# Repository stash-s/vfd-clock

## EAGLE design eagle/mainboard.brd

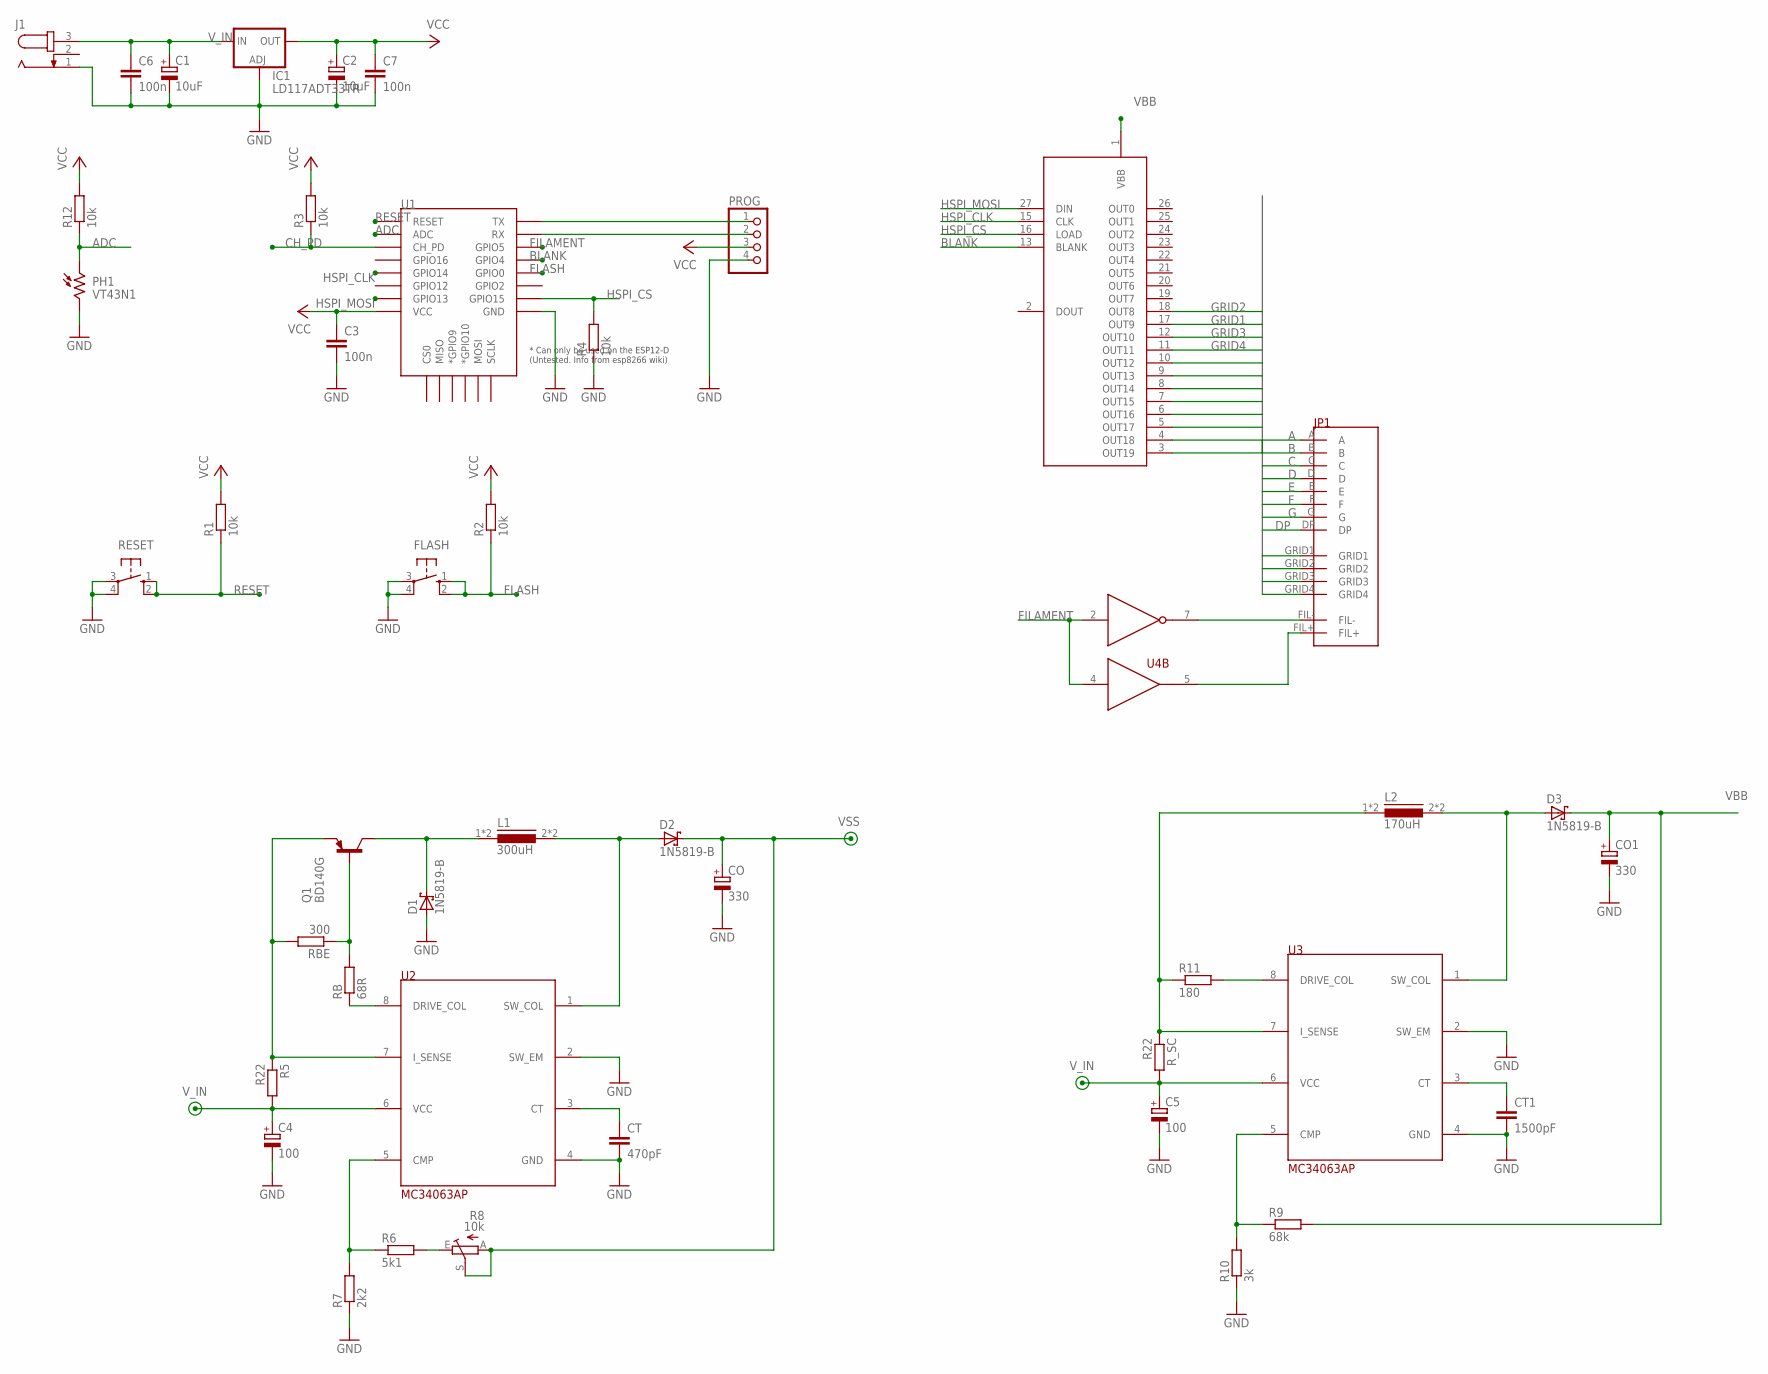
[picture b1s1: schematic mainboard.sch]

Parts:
C1, C2: 10uF; TT2D5L
C3, C6, C7: 100n; C050-024X044
C4, C5: 100; TT2D5L
CO: 330; TT5D11R
CO1: 330; TT5D11L
CT: 470pF; C025-025X050
CT1: 1500pF; C025-025X050
D1, D2, D3: 1N5819-B; DO41-7.6
FLASH: 10-XX; B3F-10XX
IC1: LD117ADT33TR; DPACK
J1: JACK-PLUG0; SPC4077
JP1: PINHD-2X102X10-MALE; 2X10
L1: 300uH; TOROID
L2: 170uH; TOROID
PH1: VT43N1; VT400
PROG: PINHD-1X4/90; 1X04/90
Q1: BD140G; TO225AA
R1, R12: 10k; 0207/15
R2, R4: 10k; 0204/7
R3: 10k; 0207/10
R5: R22; 0411/15
R6: 5k1; 0204/7
R7: 2k2; 0204/7
R8: 10k; S64W
R9: 68k; 0204/7
R10: 3k; 0204/7
R11: 180; 0204/7
RB: 68R; 0204/7
RBE: 300; 0204/7
RESET: 10-XX; B3F-10XX
R_SC: R22; 0411/15
U1: ESP12ESMD; ESP12E-SMD
U2, U3: MC34063AP; DIL8
U4: MAX628; DIL8
U$1: MAX6921AWI; SOP28X

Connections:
A: JP1.A, U$1.10 (OUT12)
ADC: PH1.1, R12.1, U1.ADC
B: JP1.B, U$1.9 (OUT13)
BLANK: U1.GPIO4, U$1.13 (BLANK)
C: JP1.C, U$1.8 (OUT14)
CH_PD: R3.1, U1.CH_PD
D: JP1.D, U$1.7 (OUT15)
DP: JP1.DP, U$1.3 (OUT19)
E: JP1.E, U$1.6 (OUT16)
F: JP1.F, U$1.5 (OUT17)
FIL+: JP1.FIL+, U4.5 (OUT)
FIL-: JP1.FIL-, U4.7 (OUT)
FILAMENT: U1.GPIO5, U4.2 (IN), U4.4 (IN)
FLASH: FLASH.1 (S), FLASH.2 (S1), R2.1, U1.GPIO0
G: JP1.G, U$1.4 (OUT18)
GND: C1.-, C2.-, C3.2, C4.-, C5.-, C6.2, C7.2, CO.-, CO1.-, CT.2, CT1.2, D1.A, FLASH.3, FLASH.4 (P1), IC1.1 (ADJ), J1.1, PH1.2, PROG.4, R4.1, R7.1, R10.1, RESET.3, RESET.4 (P1), U1.GND, U2.2 (SW_EM), U2.4 (GND), U3.2 (SW_EM), U3.4 (GND), U4.3 (GND), U$1.14 (GND)
GRID1: JP1.GRID1, U$1.17 (OUT9)
GRID2: JP1.GRID2, U$1.18 (OUT8)
GRID3: JP1.GRID3, U$1.12 (OUT10)
GRID4: JP1.GRID4, U$1.11 (OUT11)
HSPI_CLK: U1.GPIO14, U$1.15 (CLK)
HSPI_CS: R4.2, U1.GPIO15, U$1.16 (LOAD)
HSPI_MOSI: U1.GPIO13, U$1.27 (DIN)
unnamed: Q1.3 (B), RB.2, RBE.1
unnamed: RB.1, U2.8 (DRIVE_COL)
unnamed: Q1.1 (E), R5.1, RBE.2, U2.7 (I_SENSE)
unnamed: D2.A, L1.2, L1.2A (2), U2.1 (SW_COL)
unnamed: D1.C, L1.1, L1.1A (1), Q1.2 (C)
unnamed: CT.1, U2.3 (CT)
unnamed: R6.1, R7.2, U2.5 (CMP)
unnamed: R6.2, R8.E
unnamed: L2.1, L2.1A (1), R11.1, R_SC.1, U3.7 (I_SENSE)
unnamed: D3.A, L2.2, L2.2A (2), U3.1 (SW_COL)
unnamed: CT1.1, U3.3 (CT)
unnamed: R9.1, R10.2, U3.5 (CMP)
unnamed: R11.2, U3.8 (DRIVE_COL)
RESET: R1.1, RESET.1 (S), RESET.2 (S1), U1.RESET
RX: PROG.2, U1.RXD0 (RX)
TX: PROG.1, U1.TXD0 (TX)
VBB: CO1.+, D3.C, R9.2, U$1.1 (VBB)
VCC: C2.+, C3.1, C7.1, IC1.4 (OUT), PROG.3, R1.2, R2.2, R3.2, R12.2, U1.VCC, U$1.28 (VCC)
VSS: CO.+, D2.C, R8.A, R8.S, U4.6 (VSS)
V_IN: C1.+, C4.+, C5.+, C6.1, IC1.3 (IN), J1.3, R5.2, R_SC.2, U2.6 (VCC), U3.6 (VCC)

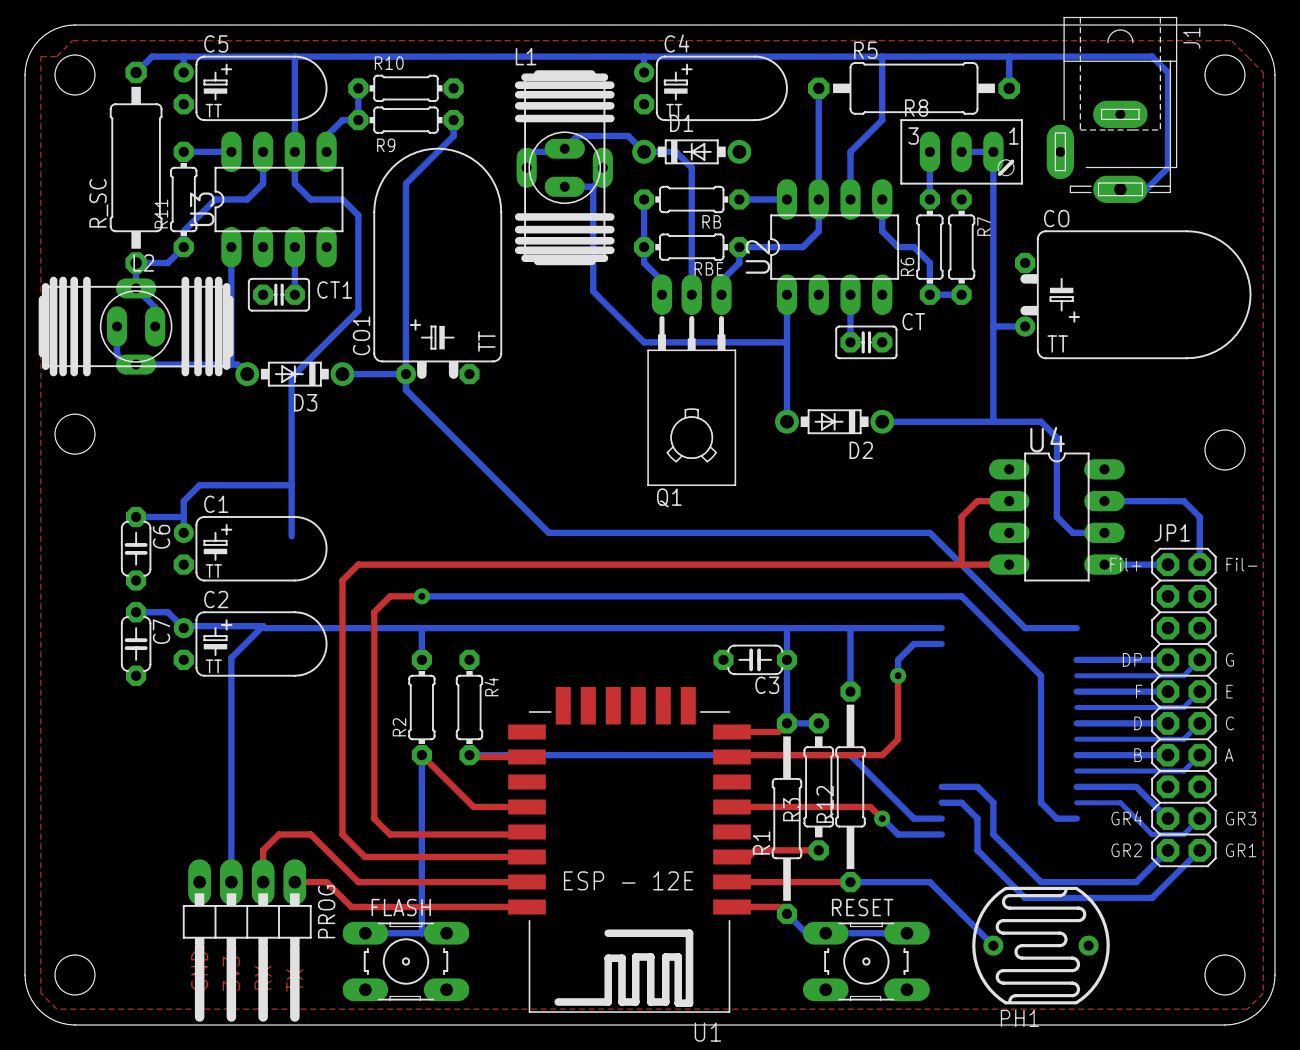
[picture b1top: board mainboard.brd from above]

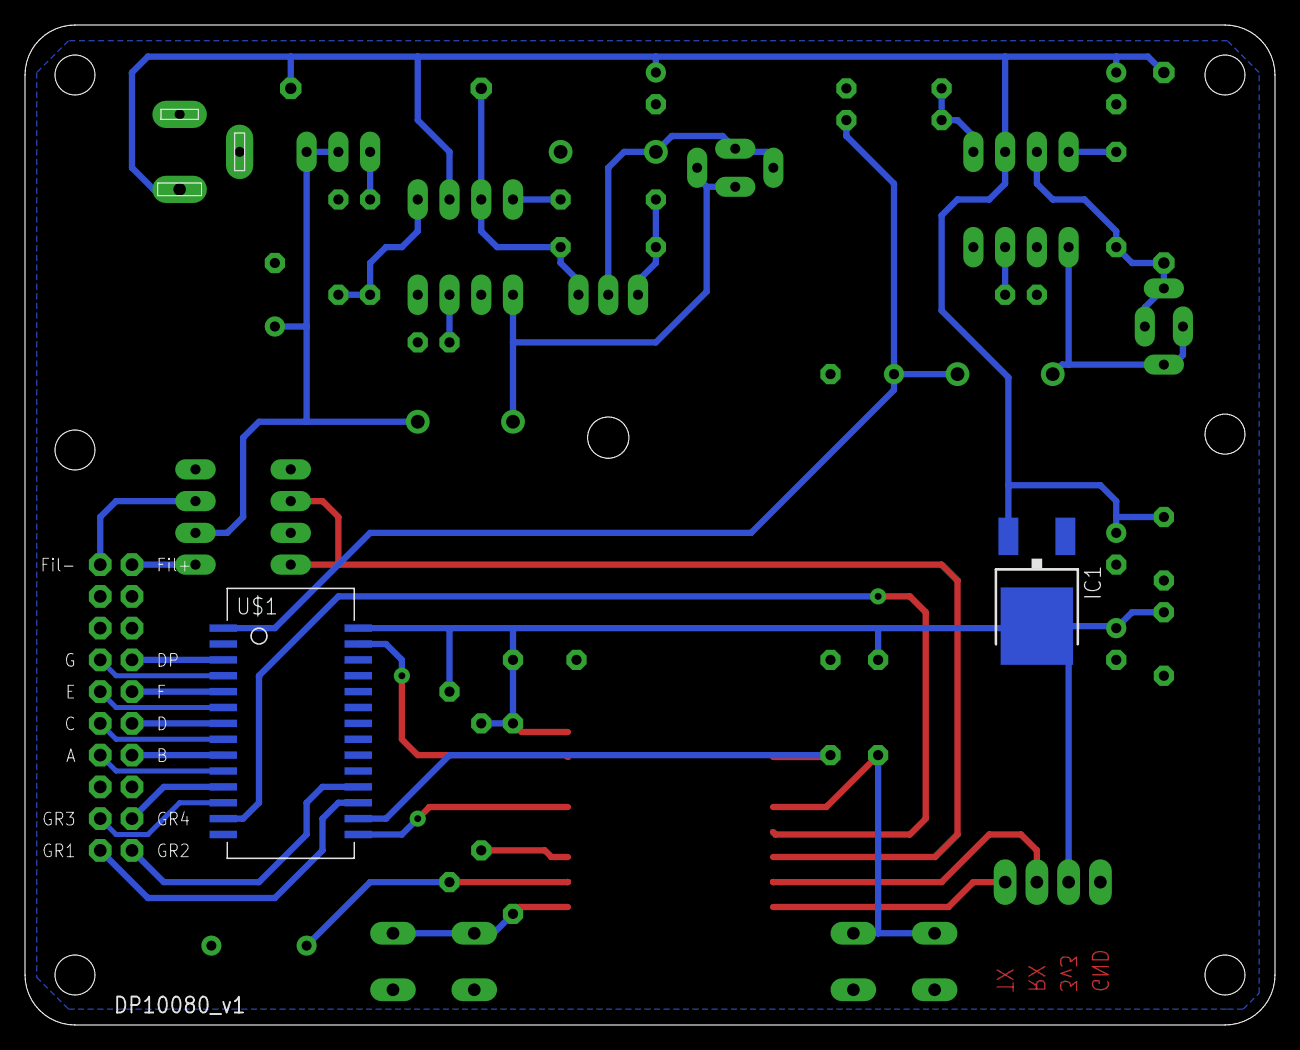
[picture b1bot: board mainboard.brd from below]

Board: 2 copper layers, 100.0 x 80.0 mm, 45 parts (2 on the bottom side), 43 nets.

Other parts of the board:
U$3: DP10080_V1

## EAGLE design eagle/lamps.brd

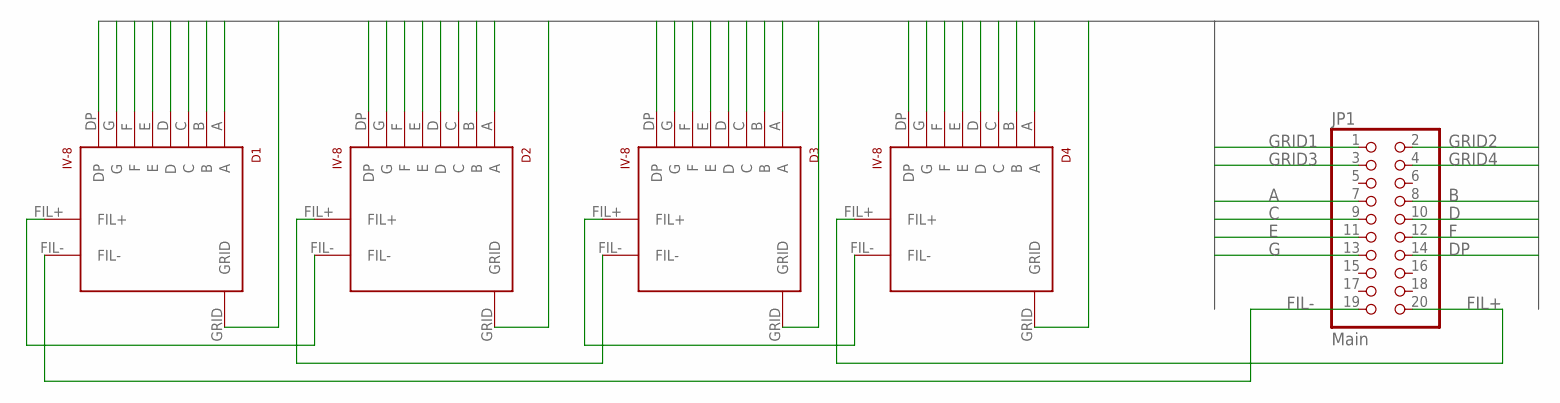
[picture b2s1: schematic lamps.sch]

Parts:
D1, D2, D3, D4: IV-8
JP1: Main; 2X10

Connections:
A: D1.A, D2.A, D3.A, D4.A, JP1.7 (A)
B: D1.B, D2.B, D3.B, D4.B, JP1.8 (B)
C: D1.C, D2.C, D3.C, D4.C, JP1.9 (C)
D: D1.D, D2.D, D3.D, D4.D, JP1.10 (D)
DP: D1.DP, D2.DP, D3.DP, D4.DP, JP1.14 (DP)
E: D1.E, D2.E, D3.E, D4.E, JP1.11 (E)
F: D1.F, D2.F, D3.F, D4.F, JP1.12 (F)
FIL+: D4.FIL+, JP1.20 (FIL+)
FIL-: D1.FIL-, JP1.19 (FIL-)
G: D1.G, D2.G, D3.G, D4.G, JP1.13 (G)
GRID1: D1.GRID, JP1.1 (GRID1)
GRID2: D2.GRID, JP1.2 (GRID2)
GRID3: D3.GRID, JP1.3 (GRID3)
GRID4: D4.GRID, JP1.4 (GRID4)
unnamed: D2.FIL+, D3.FIL-
unnamed: D1.FIL+, D2.FIL-
unnamed: D3.FIL+, D4.FIL-

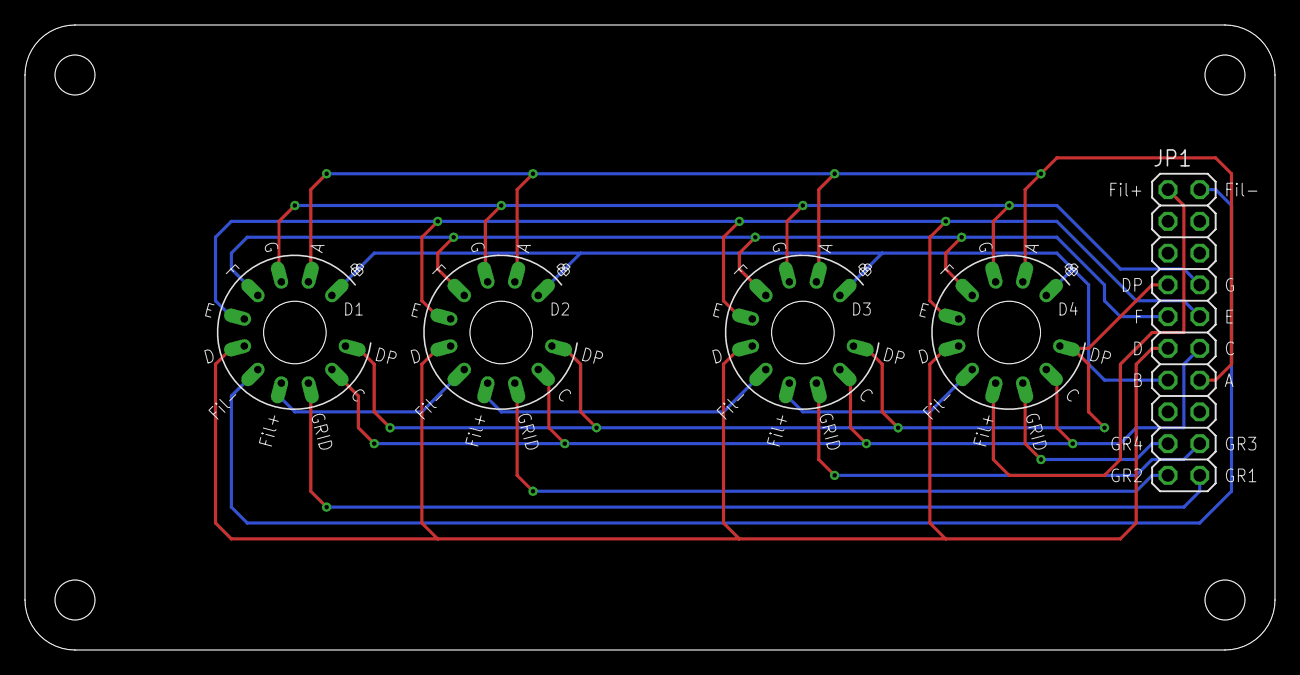
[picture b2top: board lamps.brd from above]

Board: 2 copper layers, 100.0 x 50.0 mm, 6 parts (0 on the bottom side), 17 nets.

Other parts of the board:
U$1: DP10050_V1

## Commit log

2017-10-22 Working clock, starting with timestamp provided by sketch.
2017-10-22 Main VFD driver loop works off AVR ISR call.
2017-10-22 Set pulled up 74HC595 MR pin to zero after bootup. Pulling pin up at boot time prevents constantly lit grids.
2017-10-22 Removed dead code.
2017-10-22 Cleaned up.
2017-10-22 Tried building some classes.
2017-10-24 Minor cleanup.
2017-10-24 Added funky animations on minute change.
2017-10-24 Cleanup.
2017-10-26 Working clock, reading time from RTC.
2017-11-01 adding filament pin PWM control
2017-11-03 Light dimming now works.
2017-11-25 Replaced loooong portable shiftOut calls with SPI
2017-11-26 Added doc screenshots of SPI vs. generic shiftOut.
2017-12-03 Lambdas, lambdas everywhere.
2018-02-26 Mainboard ready for printing.
